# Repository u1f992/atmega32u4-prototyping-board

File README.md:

# atmega32u4-prototyping-board

The simple development board featuring only the essential components for the ATmega32U4: bypass capacitors, USB Type-C connector, clock circuit, and a pull-up resistor for RESET.

The VBUS and 5V input lines are separated, allowing you to switch between self-powered and bus-powered modes via external wiring.

- [ATmega32U4 datasheet](https://ww1.microchip.com/downloads/en/DeviceDoc/Atmel-7766-8-bit-AVR-ATmega16U4-32U4_Datasheet.pdf)

## Ceramic Resonator Selection

The base part number of the ceramic resonator used in compact Arduino-compatible boards with the ATmega32U4 appears to be Murata's CSTNE16M0V\* ([reference](https://electronics.stackexchange.com/a/665240)). Suitable ceramic resonators can be searched using Murata’s [SimSurfing: IC-タイミングデバイス検索ツール](https://ds.murata.co.jp/simsurfing/ic-timing-device.html). Since the ATmega32U4 itself is not listed, searches were performed using ATmega32M1 and ATmega32C1 instead.

The difference between [CSTNE16M0V53C000R0](https://www.digikey.jp/ja/products/detail/murata-electronics/CSTNE16M0V53C000R0/8747730) and [CSTNE16M0VH3C000R0](https://www.digikey.jp/ja/products/detail/murata-electronics/CSTNE16M0VH3C000R0/8747732) lies in their frequency tolerance, with the latter offering higher precision. The former is more affordable, so it is the one being used.

- [CSTNE16M0V53C000R0|セラミック発振子/水晶振動子|タイミングデバイス|村田製作所](https://www.murata.com/ja-jp/products/productdetail?partno=CSTNE16M0V53C000R0)
- [CSTNE16M0V53C000R0 footprint & symbol by Murata | SnapMagic Search](https://www.snapeda.com/parts/CSTNE16M0V53C000R0/Murata/view-part/)

<details>
<summary>2025-05-09T04:07:26.697Z</summary>
<figure>
<figcaption><a href="https://ds.murata.co.jp/simsurfing/ic-timing-device.html?lcid=ja&icmaker=Microchip&icname=ATmega32M1&tdhin=CSTNE16M0V&spec_application=0&supplystatus=0&kosa=0&tempL=0&tempH=0">ATmega32M1</a></figcaption>

|IC品名|IC備考|ICメーカー|品番|適用用途[^1]|ステータス[^2]|発振周波数\[MHz]|周波数許容偏差|CL1\[pF][^3]|CL2\[pF][^4]|Rf\[ohm]|Rd\[ohm]|IC電圧(min.)\[V]|IC電圧(max.)\[V]|使用温度(min.)\[deg.C]|使用温度(max.)\[deg.C]|IC Application|
|---|---|---|---|:---:|:---:|---|---|---|---|---|---|---|---|---|---|---|
|ATmega32M1|CKSEL:111|Microchip|CSTNE16M0V53C000R0|`APS`|`生産中`|16|+/-0.5%|15|15|Open|0|4.5|5.5|-40|125||
|ATmega32M1|CKSEL:111|Microchip|CSTNE16M0VH3C000R0|`APS`|`生産中`|16|+/-0.07%|15|15|Open|0|4.5|5.5|-40|125||

</figure>

[^1]: <dl><dt><code>CE</code></dt><dd>民生機器</dd><dt><code>IE</code></dt><dd>産業機器</dd><dt><code>AIC</code></dt><dd>自動車用インフォテインメント / コンフォート機器</dd><dt><code>APS</code></dt><dd>自動車用パワートレイン / セーフティ機器</dd><dt><code>MAB</code></dt><dd>医療機器 [GHTF A/B]</dd><dt><code>MC</code></dt><dd>医療機器 [GHTF C]</dd><dt><code>MD</code></dt><dd>医療機器 [GHTF D]</dd><dt><code>MeI</code></dt><dd>インプラント除く医療機器 [GHTF A/B/C]</dd><dt><code>MI</code></dt><dd>インプラント医療機器または医療機器 [GHTF D]</dd><dt><code>MeS</code></dt><dd>インプラント・手術・自動投与用途除く医療機器 [GHTF A/B/C]</dd><dt><code>ME</code></dt><dd>モバイル機器</dd><dt><code>MC</code></dt><dd>モバイル通信</dd><dt><code>IeT</code></dt><dd>運輸・設備・商用エネルギー関連を除く産業機器</dd><dt><code>CDT</code></dt><dd>民生機器-差動伝送</dd><dt><code>HDD</code></dt><dd>HDD</dd><dt><code>DFD</code></dt><dd>重送検知</dd><dt><code>AaM</code></dt><dd>自動車用機器 <a href="https://www.murata.com/contactform?Product=Capacitor">[ムラタへ問合せ要]</a></dd><dt><code>MaM</code></dt><dd>医療機器 <a href="https://www.murata.com/contactform?Product=Capacitor">[ムラタへ問合せ要]</a></dd></dl>
[^2]: <figure><figcaption>「製品ステータス」の説明</figcaption><dl><dt><code>開発中</code></dt><dd>開発中の製品です。サンプル対応可否、量産時期についてはお問い合わせください。</dd><dt><code>生産中</code></dt><dd>量産、販売中の製品です。</dd><dt><code>NRND</code></dt><dd>新モデルへの部品採用を控えていただきたい製品です。<br>(Not Recommended for New Design)</dd><dt><code>生産中止予定</code></dt><dd>生産中止予定の製品であり、最終受注期限及び最終生産時期が表示されている場合があります。<br>最終受注期限までに、必要数量の連絡をお願いします。</dd><dt><code>生産中止</code></dt><dd>生産を中止しており、ご注文を受け付けていない製品です。</dd></dl></figure>
[^3]: 水晶振動子：外付け容量<br>セラロック：内蔵容量
[^4]: 水晶振動子：外付け容量<br>セラロック：内蔵容量

<figure>
<figcaption><a href="https://ds.murata.co.jp/simsurfing/ic-timing-device.html?lcid=ja&icmaker=Microchip&icname=ATmega32C1&tdhin=CSTNE16M0V&spec_application=0&supplystatus=0&kosa=0&tempL=0&tempH=0">ATmega32C1</a></figcaption>

|IC品名|IC備考|ICメーカー|品番|適用用途[^1]|ステータス[^2]|発振周波数\[MHz]|周波数許容偏差|CL1\[pF][^3]|CL2\[pF][^4]|Rf\[ohm]|Rd\[ohm]|IC電圧(min.)\[V]|IC電圧(max.)\[V]|使用温度(min.)\[deg.C]|使用温度(max.)\[deg.C]|IC Application|
|---|---|---|---|:---:|:---:|---|---|---|---|---|---|---|---|---|---|---|
|ATmega32C1|CKSEL:111|Microchip|CSTNE16M0V53C000R0|`APS`|`生産中`|16|+/-0.5%|15|15|Open|0|4.5|5.5|-40|125||
|ATmega32C1|CKSEL:111|Microchip|CSTNE16M0VH3C000R0|`APS`|`生産中`|16|+/-0.07%|15|15|Open|0|4.5|5.5|-40|125||

</figure>
</details>

## License

The design data for this board is provided under the CERN-OHL-S license. However, the symbol, footprint, and 3D model for library/CSTNE16M0V53C000R0 are provided via SnapMagic Search and are licensed under CC BY-SA (Design Exception 1.0) ([reference](https://www.snapeda.com/about/FAQ/#license)).

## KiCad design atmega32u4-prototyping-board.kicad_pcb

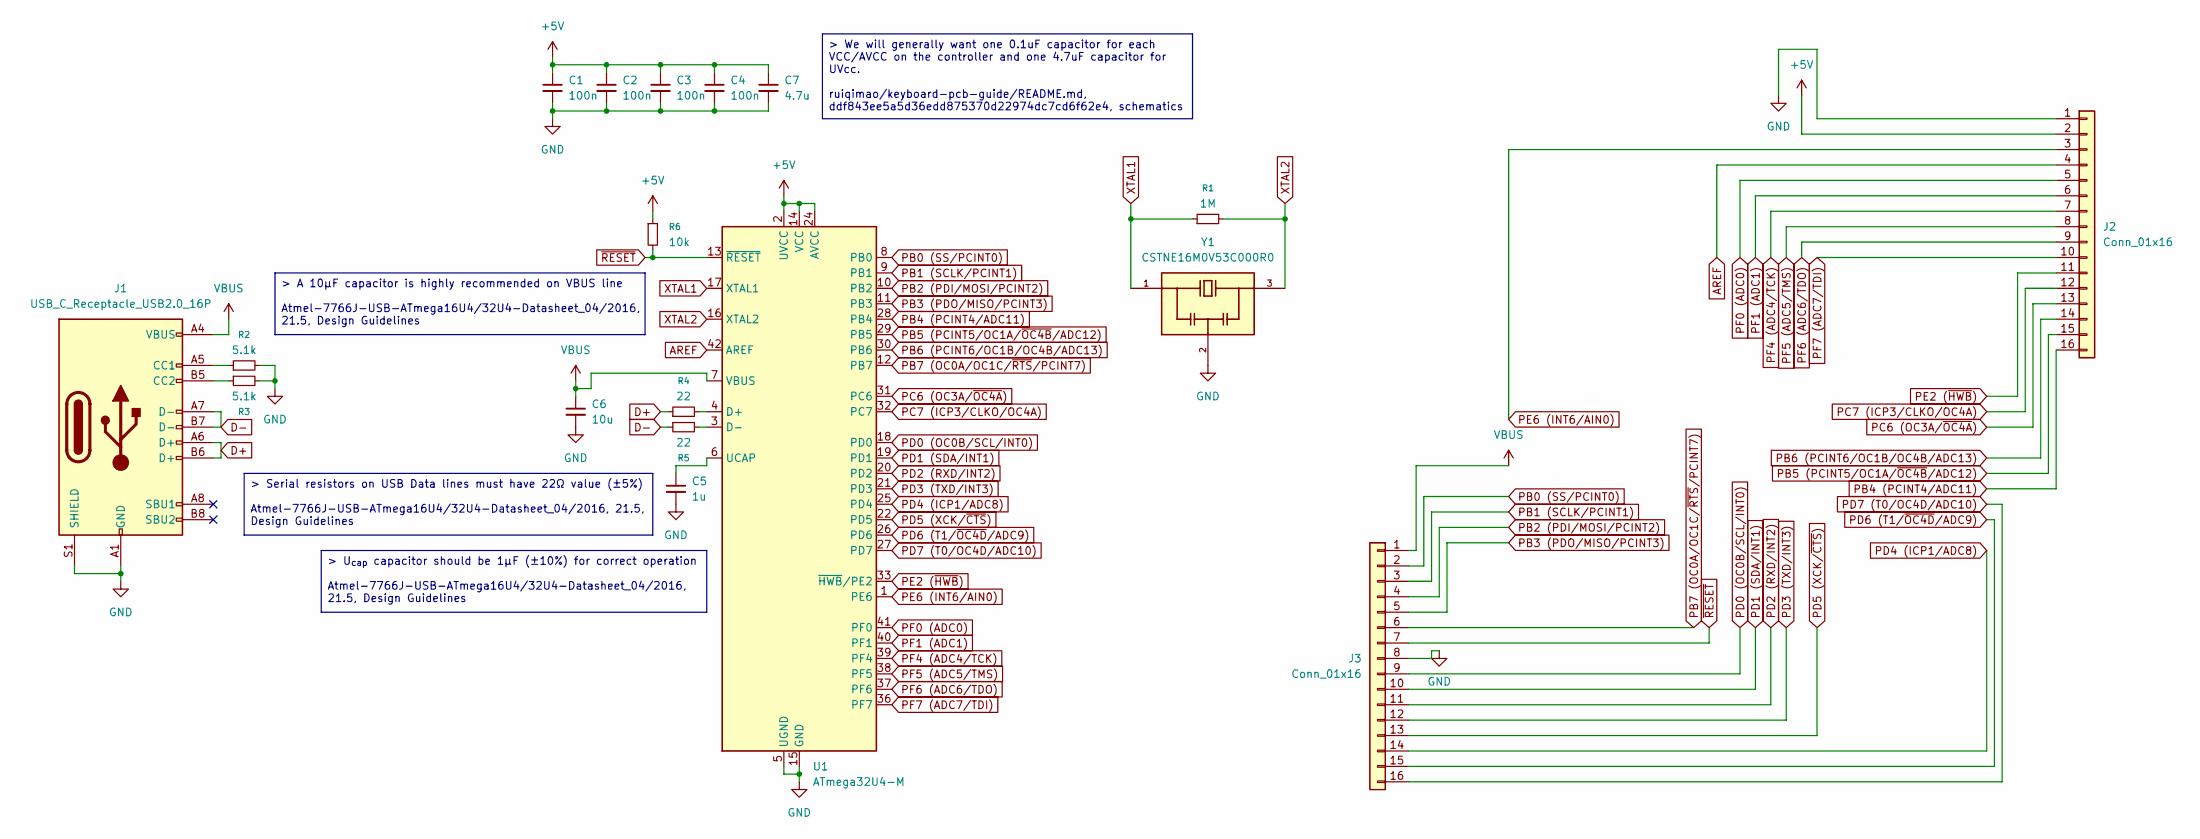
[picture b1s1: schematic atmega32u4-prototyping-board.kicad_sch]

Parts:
C1, C2, C3, C4: 100n; C_0402_1005Metric
C5: 1u; C_0402_1005Metric
C6: 10u; C_0402_1005Metric
C7: 4.7u; C_0402_1005Metric
J1: USB_C_Receptacle_USB2.0_16P; USB_C_Receptacle_HRO_TYPE-C-31-M-12
J2, J3: Conn_01x16; PinHeader_1x16_P2.54mm_Vertical
R1: 1M; R_0402_1005Metric
R2, R3: 5.1k; R_0402_1005Metric
R4, R5: 22; R_0402_1005Metric
R6: 10k; R_0402_1005Metric
U1: ATmega32U4-M; QFN-44-1EP_7x7mm_P0.5mm_EP5.2x5.2mm
Y1: CSTNE16M0V53C000R0; OSC_CSTNE16M0V53C000R0; PARTREV JGC42-8853B

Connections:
+5V: C1.1, C2.1, C3.1, C4.1, C7.1, J2.2, R6.1, U1.2 (UVCC), U1.14 (VCC), U1.24 (AVCC), U1.34 (VCC), U1.44 (AVCC)
AREF: J2.4, U1.42 (AREF)
D+: J1.A6 (D+), J1.B6 (D+), R4.1
D-: J1.A7 (D-), J1.B7 (D-), R5.1
GND: C1.2, C2.2, C3.2, C4.2, C5.2, C6.2, C7.2, J1.A1 (GND), J1.A12 (GND), J1.B1 (GND), J1.B12 (GND), J1.S1 (SHIELD), J2.1, J3.8, R2.2, R3.2, U1.5 (UGND), U1.15 (GND), U1.23 (GND), U1.35 (GND), U1.43 (GND), U1.45 (GND), Y1.2
unnamed: J1.A5 (CC1), R2.1
unnamed: J1.B5 (CC2), R3.1
unnamed: R4.2, U1.4 (D+)
unnamed: R5.2, U1.3 (D-)
unnamed: C5.1, U1.6 (UCAP)
PB0 (SS/PCINT0): J3.2, U1.8 (PB0)
PB1 (SCLK/PCINT1): J3.3, U1.9 (PB1)
PB2 (PDI/MOSI/PCINT2): J3.4, U1.10 (PB2)
PB3 (PDO/MISO/PCINT3): J3.5, U1.11 (PB3)
PB4 (PCINT4/ADC11): J2.16, U1.28 (PB4)
PB5 (PCINT5/OC1A/~OC4B/ADC12): J2.15, U1.29 (PB5)
PB6 (PCINT6/OC1B/OC4B/ADC13): J2.14, U1.30 (PB6)
PB7 (OC0A/OC1C/~RTS/PCINT7): J3.6, U1.12 (PB7)
PC6 (OC3A/~OC4A): J2.13, U1.31 (PC6)
PC7 (ICP3/CLKO/OC4A): J2.12, U1.32 (PC7)
PD0 (OC0B/SCL/INT0): J3.9, U1.18 (PD0)
PD1 (SDA/INT1): J3.10, U1.19 (PD1)
PD2 (RXD/INT2): J3.11, U1.20 (PD2)
PD3 (TXD/INT3): J3.12, U1.21 (PD3)
PD4 (ICP1/ADC8): J3.14, U1.25 (PD4)
PD5 (XCK/~CTS): J3.13, U1.22 (PD5)
PD6 (T1/~OC4D/ADC9): J3.15, U1.26 (PD6)
PD7 (T0/OC4D/ADC10): J3.16, U1.27 (PD7)
PE2 (~HWB): J2.11, U1.33 (~HWB/PE2)
PE6 (INT6/AIN0): J2.3, U1.1 (PE6)
PF0 (ADC0): J2.5, U1.41 (PF0)
PF1 (ADC1): J2.6, U1.40 (PF1)
PF4 (ADC4/TCK): J2.7, U1.39 (PF4)
PF5 (ADC5/TMS): J2.8, U1.38 (PF5)
PF6 (ADC6/TDO): J2.9, U1.37 (PF6)
PF7 (ADC7/TDI): J2.10, U1.36 (PF7)
VBUS: C6.1, J1.A4 (VBUS), J1.A9 (VBUS), J1.B4 (VBUS), J1.B9 (VBUS), J3.1, U1.7 (VBUS)
XTAL1: R1.1, U1.17 (XTAL1), Y1.1
XTAL2: R1.2, U1.16 (XTAL2), Y1.3
~RESET: J3.7, R6.2, U1.13 (~RESET)

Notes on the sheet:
> A 10µF capacitor is highly recommended on VBUS line Atmel-7766J-USB-ATmega16U4/32U4-Datasheet_04/2016, 21.5, Design Guidelines
> U_{cap} capacitor should be 1µF (±10%) for correct operation Atmel-7766J-USB-ATmega16U4/32U4-Datasheet_04/2016, 21.5, Design Guidelines
> Serial resistors on USB Data lines must have 22Ω value (±5%) Atmel-7766J-USB-ATmega16U4/32U4-Datasheet_04/2016, 21.5, Design Guidelines
> We will generally want one 0.1uF capacitor for each VCC/AVCC on the controller and one 4.7uF capacitor for UVcc. ruiqimao/keyboard-pcb-guide/README.md, ddf843ee5a5d36edd875370d22974dc7cd6f62e4, schematics

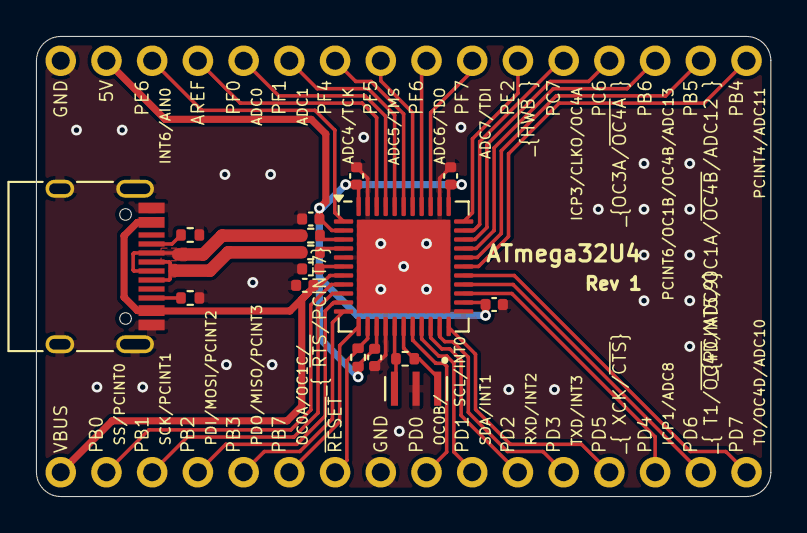
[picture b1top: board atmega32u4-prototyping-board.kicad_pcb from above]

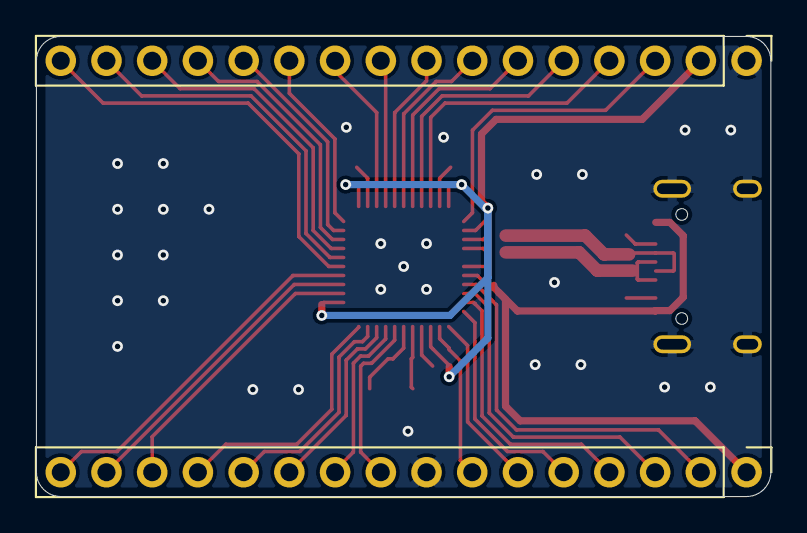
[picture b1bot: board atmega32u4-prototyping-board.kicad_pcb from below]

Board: 2 copper layers, 40.8 x 25.6 mm, 18 parts (2 on the bottom side), 40 nets.

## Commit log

2025-05-17 Add .gitignore
2025-05-18 tutorial/blink
2025-05-18 Move files
2025-05-18 Add submodule
2025-05-18 Fix DP DM connections
2025-05-18 Update board image
